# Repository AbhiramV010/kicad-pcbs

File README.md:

# kicad-pcbs
All the PCBs I've made on my journey through the world of board design. 
***
DISCLAIMER: If you do choose to make/manufacture any of the circuits from this repo or from my profile as a whole, I will not be responsible for any damage(s) that may be caused as a result, whether direct or indirect.
***

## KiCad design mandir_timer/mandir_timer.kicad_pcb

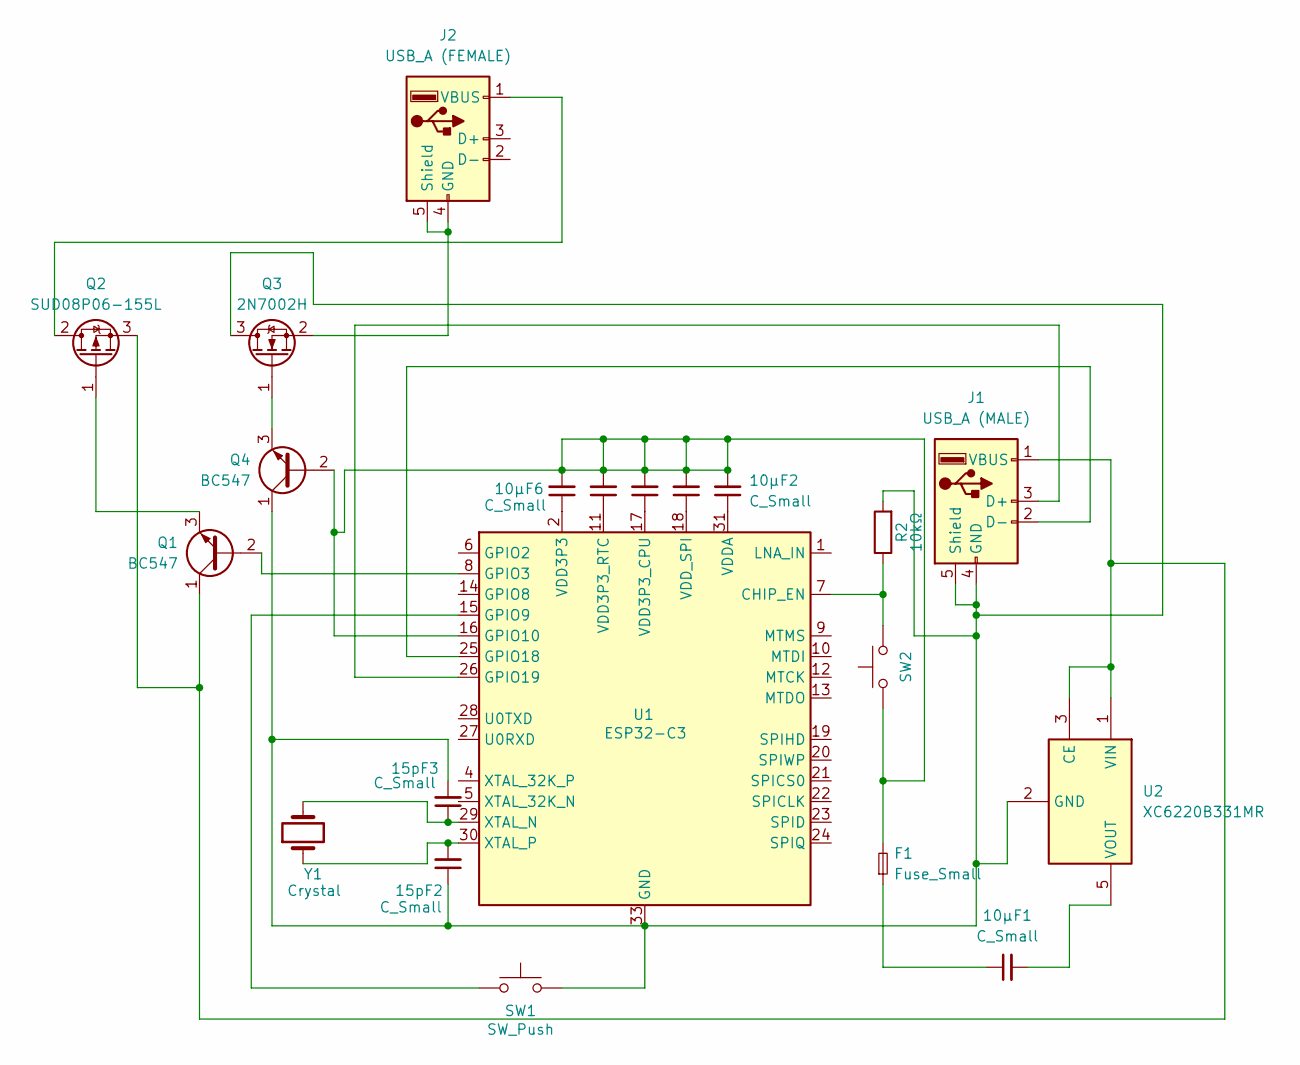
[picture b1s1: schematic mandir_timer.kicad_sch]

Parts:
0.1µF1, 0.1µF2, 1µF1, 10µF1, 10µF2, 10µF6, 15pF2, 15pF3: C_Small; C_1210_3225Metric
F1: Fuse_Small; Fuse_1210_3225Metric
J1: USB_A (MALE); USB_A_CNCTech_1001-011-01101_Horizontal
J2: USB_A (FEMALE); USB_A_TE_292303-7_Horizontal
Q1, Q4: BC547; SOT-23
Q2: SUD08P06-155L; TO-252-2
Q3: 2N7002H; SOT-23
R2: 10kΩ; R_Axial_DIN0204_L3.6mm_D1.6mm_P1.90mm_Vertical
SW1: SW_Push; SW_PUSH_6mm_H9.5mm
SW2: SW_Push; SW_PUSH_6mm_H4.3mm
U1: ESP32-C3; QFN-32-1EP_4x4mm_P0.4mm_EP2.9x2.9mm
U2: XC6220B331MR; SOT-23-5
Y1: Crystal; Crystal_SMD_MicroCrystal_CC5V-T1A-2Pin_4.1x1.5mm

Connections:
unnamed: 10µF1.1, F1.1
unnamed: 10µF2.1, U1.31 (VDDA), U1.32 (VDDA)
unnamed: 10µF6.1, U1.2 (VDD3P3), U1.3 (VDD3P3)
unnamed: J1.3 (D+), U1.26 (GPIO19)
unnamed: J1.2 (D-), U1.25 (GPIO18)
unnamed: 15pF2.1, 15pF3.2, J1.4 (GND), J1.5 (Shield), Q3.3 (D), Q4.1 (C), R2.2, SW1.2, U1.33 (GND), U2.2 (GND)
unnamed: J1.1 (VBUS), Q1.1 (C), Q2.3 (S), U2.1 (VIN), U2.3 (CE)
unnamed: J2.4 (GND), J2.5 (Shield), Q3.2 (S)
unnamed: J2.1 (VBUS), Q2.2 (D)
unnamed: Q1.2 (B), U1.8 (GPIO3)
unnamed: Q1.3 (E), Q2.1 (G)
unnamed: Q3.1 (G), Q4.3 (E)
unnamed: 0.1µF1.2, 0.1µF2.2, 1µF1.2, 10µF2.2, 10µF6.2, F1.2, Q4.2 (B), SW2.1, U1.16 (GPIO10)
unnamed: R2.1, SW2.2, U1.7 (CHIP_EN)
unnamed: SW1.1, U1.15 (GPIO9)
unnamed: 0.1µF2.1, U1.17 (VDD3P3_CPU)
unnamed: 0.1µF1.1, U1.11 (VDD3P3_RTC)
unnamed: 1µF1.1, U1.18 (VDD_SPI)
unnamed: 15pF3.1, U1.29 (XTAL_N), Y1.2
unnamed: 15pF2.2, U1.30 (XTAL_P), Y1.1
unnamed: 10µF1.2, U2.5 (VOUT)

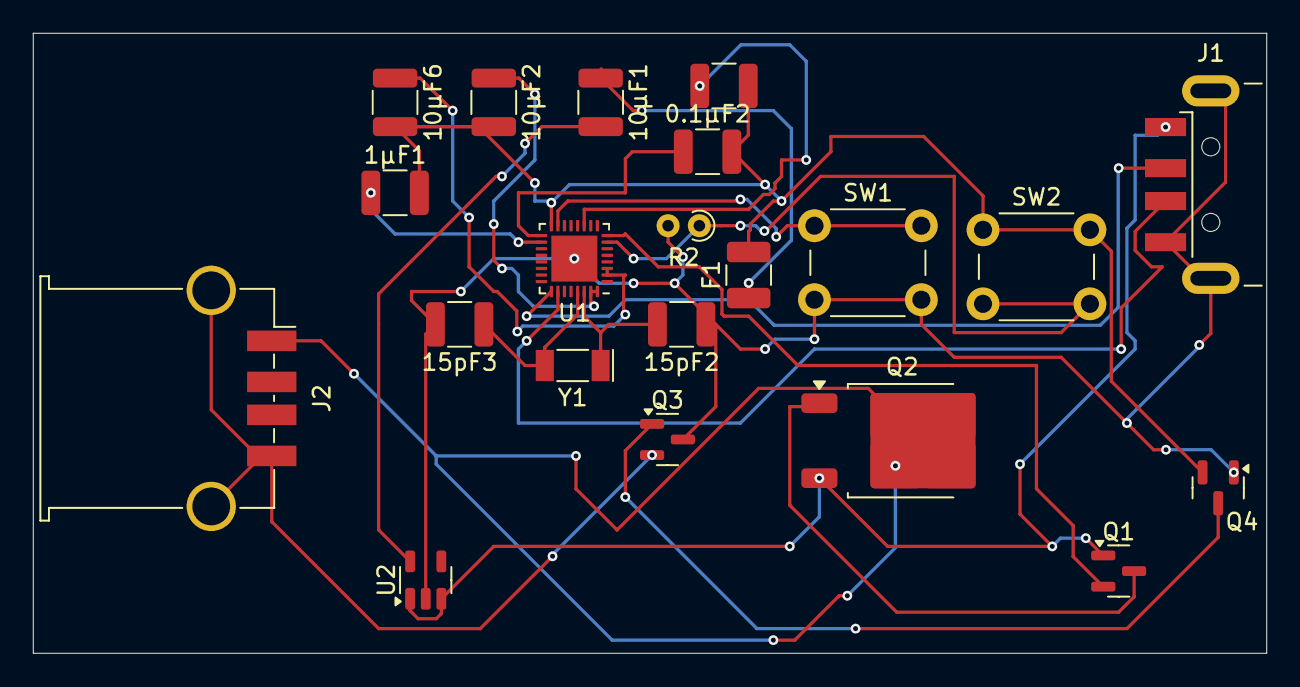
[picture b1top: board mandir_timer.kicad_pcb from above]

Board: 2 copper layers, 75.0 x 37.7 mm, 21 parts (0 on the bottom side), 21 nets.

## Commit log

2026-03-18 Create a
2026-03-18 Created & added the files for mandir_timer
    This project was made to control the lights on a prayer table, turning them on and off at specific times of day.
2026-03-18 Add disclaimer about circuit manufacturing responsibility
    Added a disclaimer regarding responsibility for circuit damage.
2026-03-19 Add disclaimer to README about circuit safety
    Added a disclaimer regarding the responsibility for circuit damage.
